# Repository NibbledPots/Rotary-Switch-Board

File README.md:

# Rotary-Switch-Board
Board for 1P8T SR16 switch to allow for one arduino input using voltage dividers
based on [this tutorial](https://www.youtube.com/watch?v=UbnNhUDheE8). All basic coding information can also be found using that video.

I used this to replicate rotary switches in the DCS F-14, but it can have other purposes

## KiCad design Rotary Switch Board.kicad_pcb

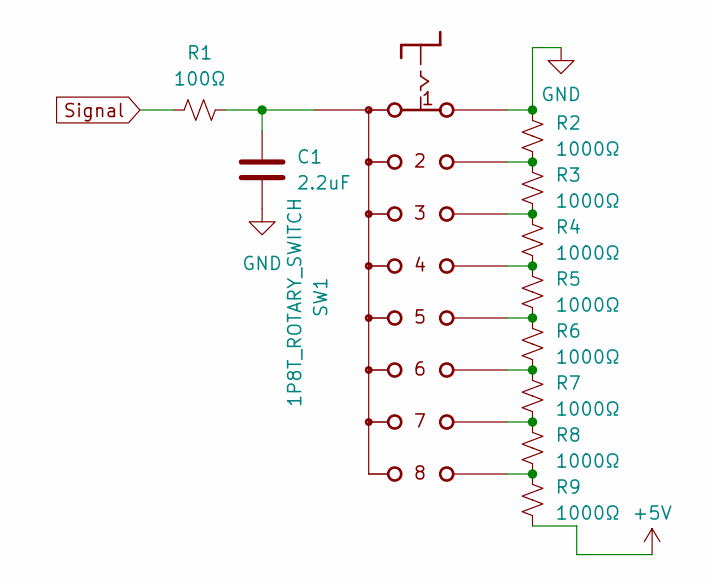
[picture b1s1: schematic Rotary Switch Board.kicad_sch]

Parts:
C1: 2.2uF; CP_Radial_Tantal_D5.0mm_P5.00mm
R1: 100Ω; R_Axial_DIN0204_L3.6mm_D1.6mm_P5.08mm_Horizontal
R2, R3, R4, R5, R6, R7, R8, R9: 1000Ω; R_Axial_DIN0204_L3.6mm_D1.6mm_P5.08mm_Horizontal
SW1: 1P8T_ROTARY_SWITCH; 1P8T

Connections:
+5V: R9.2
GND: C1.2, R2.1, SW1.1; also elsewhere on the board
unnamed: C1.1, R1.2, SW1.9
unnamed: R2.2, R3.1, SW1.2
unnamed: R3.2, R4.1, SW1.3
unnamed: R4.2, R5.1, SW1.4
unnamed: R5.2, R6.1, SW1.5
unnamed: R6.2, R7.1, SW1.6
unnamed: R7.2, R8.1, SW1.7
unnamed: R8.2, R9.1, SW1.8
Signal: R1.1

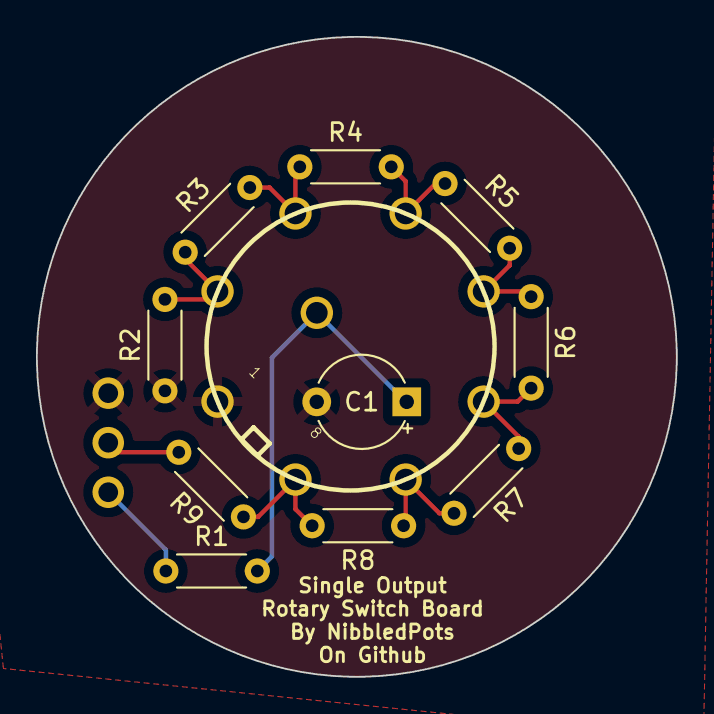
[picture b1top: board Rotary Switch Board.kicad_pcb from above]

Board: 2 copper layers, 35.5 x 35.5 mm, 12 parts (1 on the bottom side), 9 nets.

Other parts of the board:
J6: D2; SinglePad

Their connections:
GND: J6.1; also elsewhere on the board

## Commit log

2023-07-07 Created PCB
2023-07-08 added Silkscreen decorations
2023-07-17 Added GND planes
2023-07-22 fixed(?) text
2023-07-22 included larger resistor
2023-07-31 allowed for connection of all 8 pins, now you can just skip the ones you dont need
    now you can just skip the ones you dont need
2023-07-31 redid traces
